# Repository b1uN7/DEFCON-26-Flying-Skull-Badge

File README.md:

DEFCON 26 Flying Skull Badge

__Let's wotk together for DEFCON 29 (2021)!!  I have set up a new Slack fir us to prepare: 
https://join.slack.com/t/flyingbadgers/shared_invite/zt-rhldgde9-1GLsEr0Yzdh6VICE2oVjuQ__

/------------------------------------------------------------------------------------------------\\ 

| . .  . * READ ME * . . . * NO SHIT READ ME * . . . *You will be F#@KED if you don't READ ME!!!*  . . . |

/------------------------------------------------------------------------------------------------\\ 

|--------------------__I have figured the following items out _the hard way_!!!__-----------------------|

/------------------------------------------------------------------------------------------------\\ 

| 1 DO NOT CROSS NEG & POS -/+ there is no protection for this (ie soldering on battery leads!) 

| 2 DO NOT solder RED FCU Board more then 3 SECS!  Diods will POP & NEED TO BUY NEW ONES!

| 3 If RED FCU Board from Syma 5X is solid RED (no blink) when powered see #2!!

| 4 Propellors are different (A & B) be sure to MATCH them to the MOTORS (See badge around motors!)

/------------------------------------------------------------------------------------------------\\

*** QUICK UPDATE: GETTING STARTED WITH YOU BADGE ***                   

*** (AKA GETTING YOUR BADGE STARTED) VIDEO IS NOW POSTED TO WIKI ***

Ok, so if you are here, you are probably looking for flying badge stuff like "how the f*$K do I put this thing together" or "it won't stop bliking, why won't it stop blinking"

This site (in time) will answer all those questions.

For now, until I can get stuff up on Thursday (I won't commit to which Thursday I am talking about) here are the answers to those questions:

Q1: How to put it together?

A1: If you are a hacker, figure it out!  If you are not a hacker, why the f*%K do you have a hacker badge? 

Q2: How do I get this stupid-ass badge to stop blinking?

A2: See Q1

Ok, only kidding.  If you don't have a sense of humor and you expect everything to be perfect, then "this is not the badge you are looking for" <virtual hand swipe>

If you are here, then you probably know me enough to realize if it took me a year longer to get you your badge, then you will have figured out I am behind on the documentation (*WHAT, you say, I DIDN'T DO THE DOCUMENTATION FIRST OR ALONG THE WAY???  WTF???)

So be patient and lets work together.  I will be using this repository's wiki to post a lot of the stuff you are looking for (build instructions, videos, my home address so you can come kick me in the balls for making this stupid badge, etc).  As we are a hacker community, it would be great if we worked together and post all our combined shit there!  PLEASE be and ACTIVE part of this process!!  I encourage you to post, advise, answer, and collectively curse at me for doing this to you!!

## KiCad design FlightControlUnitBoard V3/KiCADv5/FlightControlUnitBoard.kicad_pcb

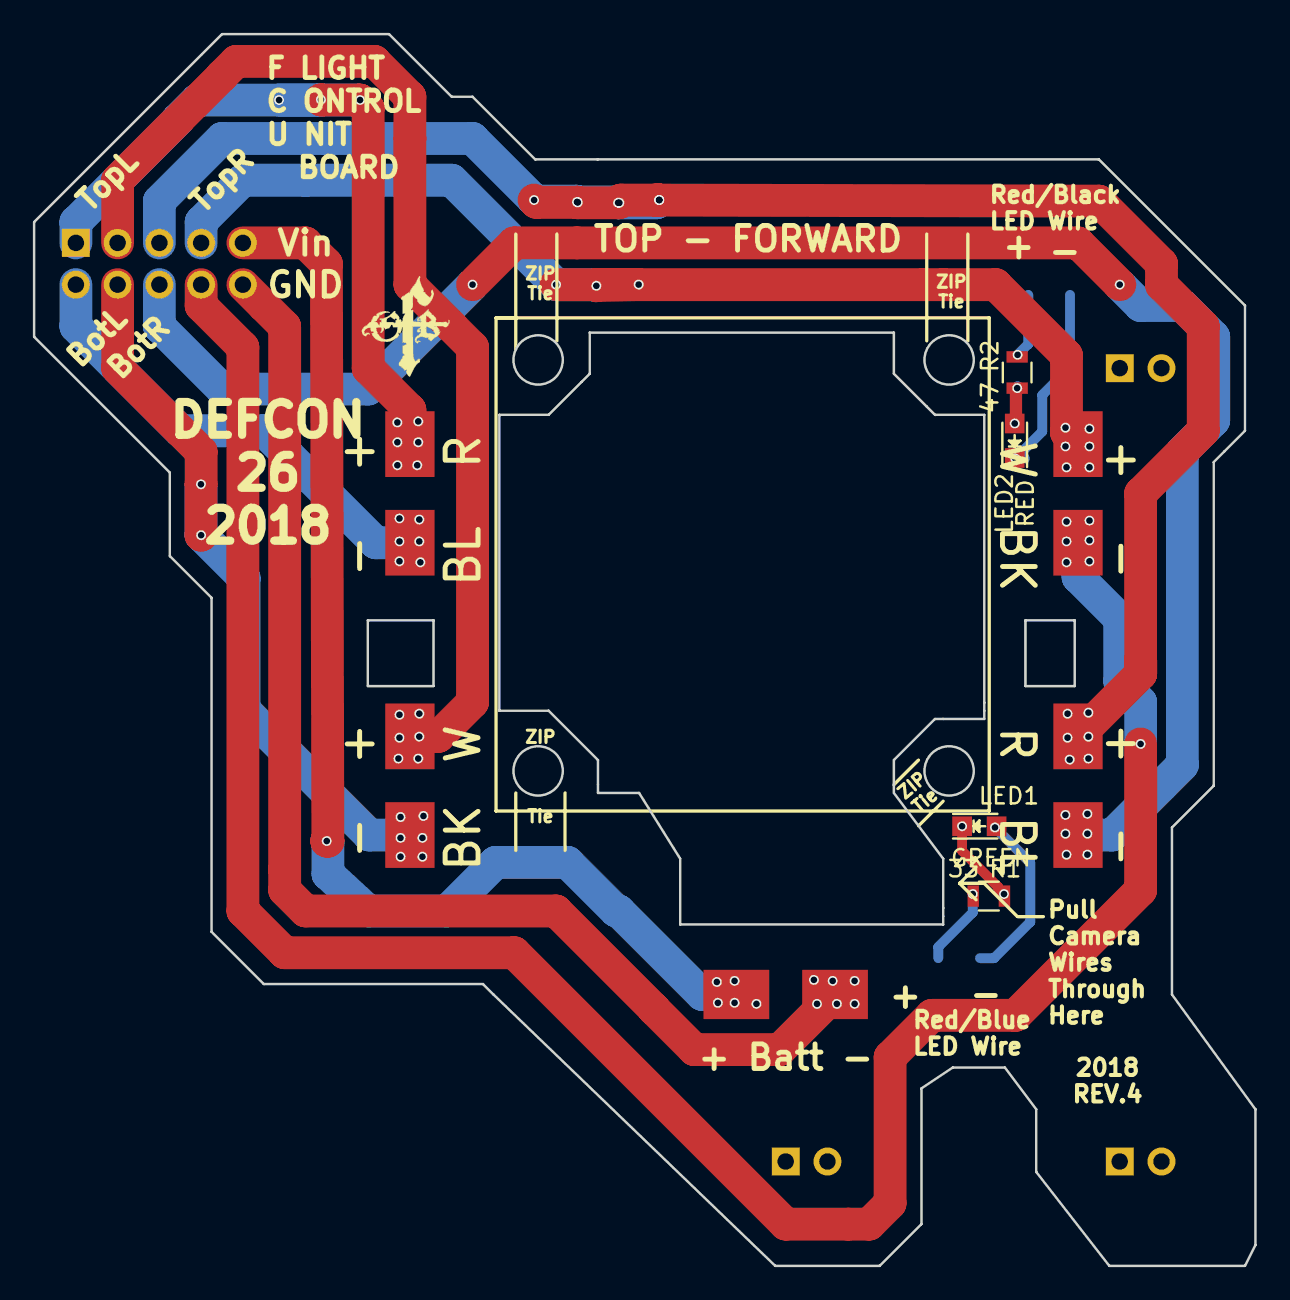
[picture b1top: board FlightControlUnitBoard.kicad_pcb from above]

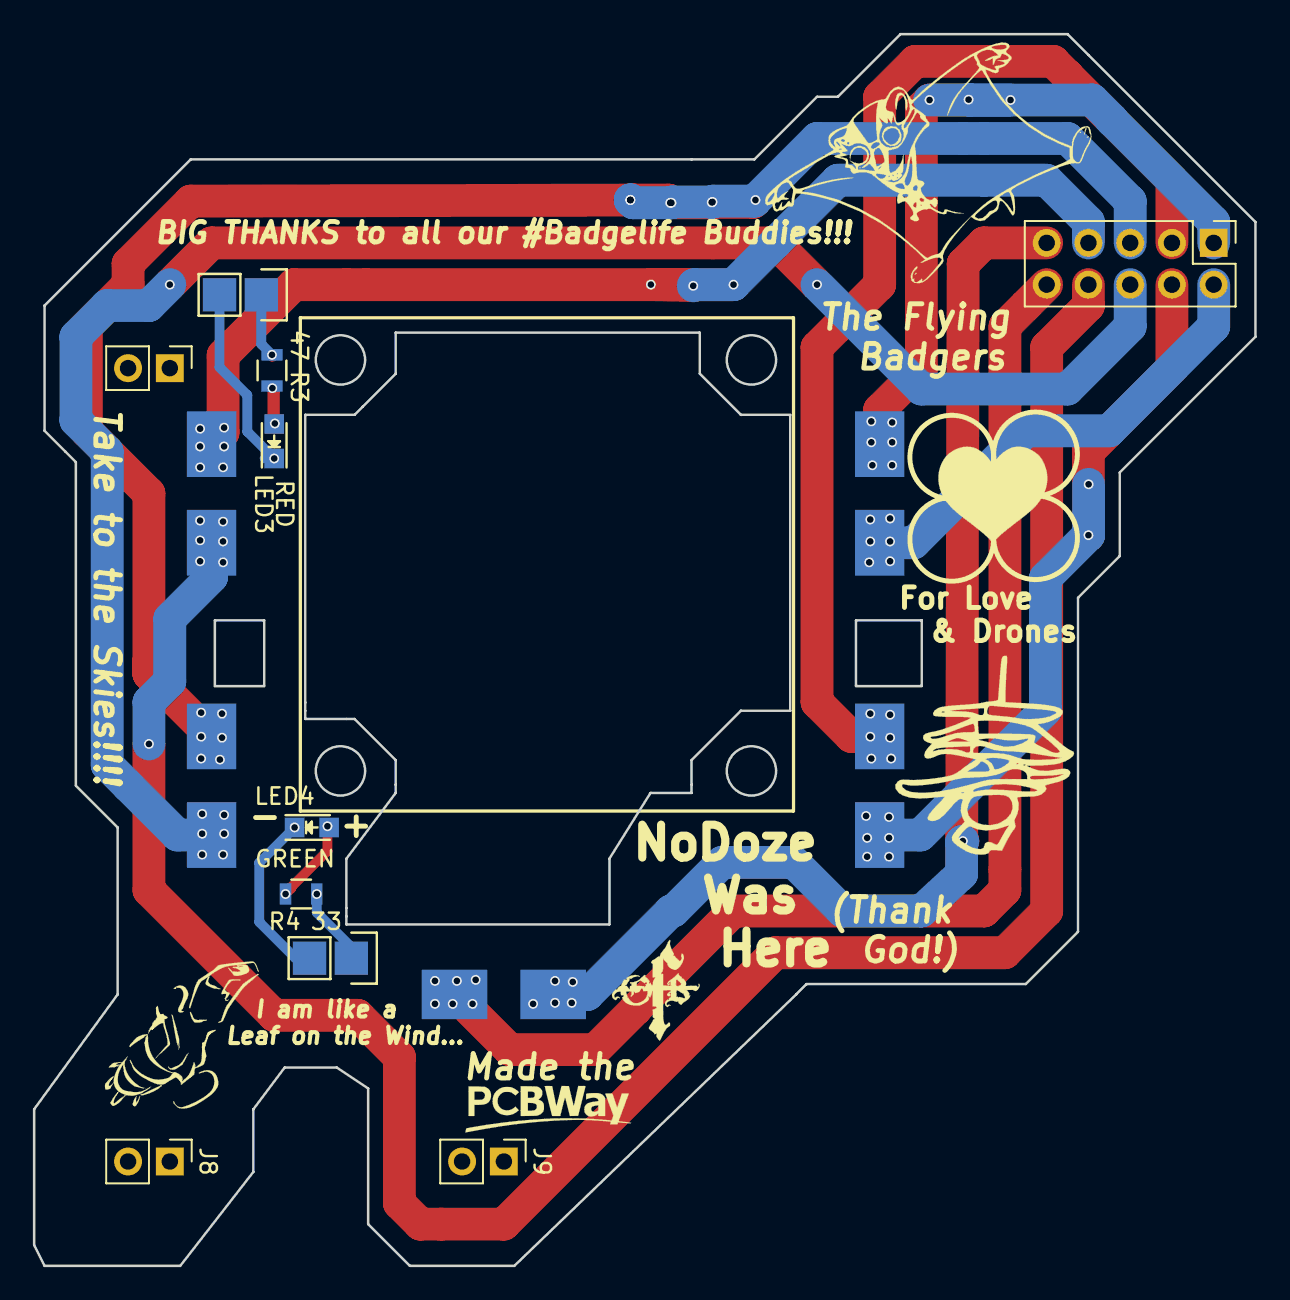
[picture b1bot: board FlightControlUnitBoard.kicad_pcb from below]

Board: 2 copper layers, 74.3 x 74.9 mm, 24 parts (15 on the bottom side), 10 nets.

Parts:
J1: Conn_02x05_Odd_Even; Pin_Header_Straight_2x05_Pitch2.54mm
J2, J2#2, J3, J3#2, J4, J4#2, J5, J5#2, J6, J6#2: Conn_01x02_Male; Wire_Pads_1x2_4x3mm
J7, J8, J9: Conn_02x01; Pin_Header_Straight_1x02_Pitch2.54mm
J10, J11: Pin_Header_Straight_1x02
LED1, LED4: GREEN; LED_0805
LED2, LED3: RED; LED_0805
R1, R4: 33; R_0805
R2, R3: 47; R_0805

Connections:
unnamed: J1.1, J3.1, J3#2.1
unnamed: J1.2, J3.2, J3#2.2
unnamed: J1.3, J4.1, J4#2.1
unnamed: J1.4, J4.2, J4#2.2
unnamed: J1.5, J6.1, J6#2.1
unnamed: J1.6, J6.2, J6#2.2
unnamed: J1.7, J5.1, J5#2.1
unnamed: J1.8, J5.2, J5#2.2
unnamed: J1.9, J2.2, J2#2.2, J9.2
unnamed: J1.10, J2.1, J2#2.1, J9.1

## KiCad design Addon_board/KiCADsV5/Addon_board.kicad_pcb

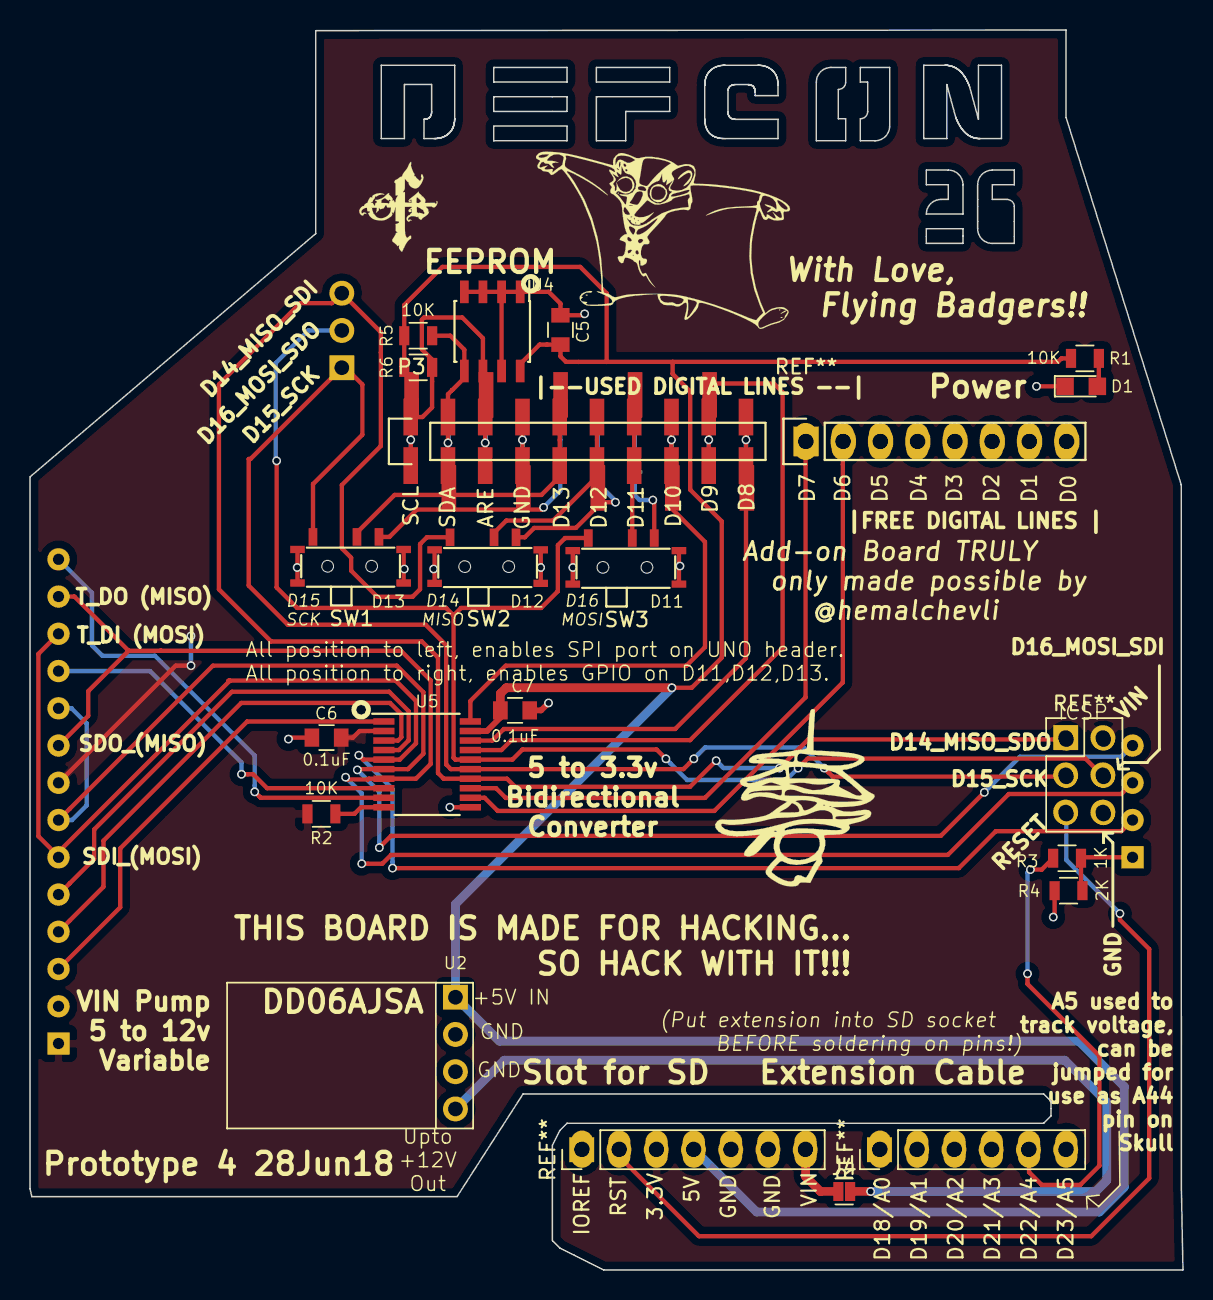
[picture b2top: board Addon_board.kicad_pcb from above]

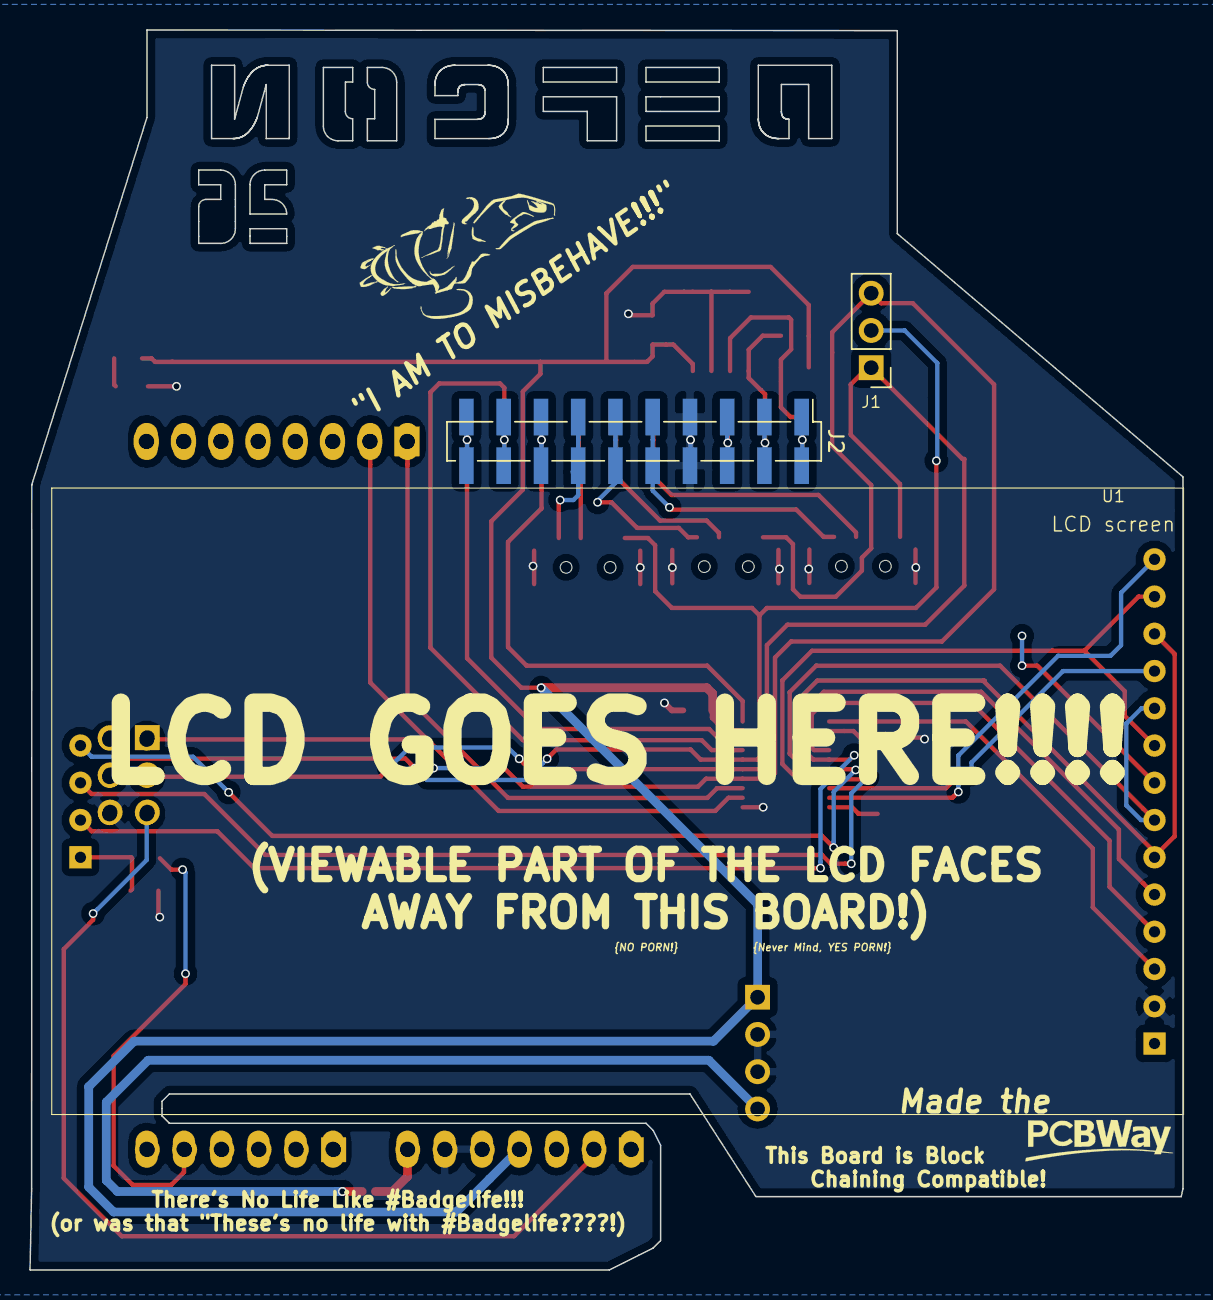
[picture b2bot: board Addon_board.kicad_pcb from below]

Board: 2 copper layers, 78.6 x 84.5 mm, 22 parts (3 on the bottom side), 35 nets.

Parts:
C5: 10 pF; C_0805
C6, C7: 0.1uF; C_0805
D1: LED; LED_0805
J1: SPI; Pin_Header_Straight_1x03_Pitch2.54mm
J2: BottomConn; Pin_Header_Straight_1x10_Pitch2.54mm_SMD_Pin1Left
J4: GS2; SolderJumper
P3: Digital Header 02; Socket_Strip_Straight_1x10_2.54_SMD
R1, R2, R5, R6: 10K; R_0805
R3: 1K; R_0805
R4: 2K; R_0805
SW1, SW2, SW3: SW_SPDT; MSK12C02
U1: 2.4TFT_LCD; 2.4_TFT_LCD_OUTLINE
U2: DD06AJSA; DCDC_BOOST
U4: 24LC256; SOIC-8_3.9x4.9mm_Pitch1.27mm
U5: TXB0108PWR; TSSOP-20_4.4x6.5mm_Pitch0.65mm
XA2: Shield; UNO_headersICSP_EDIT_10smd

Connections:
/+3V3: C6.1, R2.2, U1.1, U1.8, U5.2, XA2.3V3, XA2.SP2
/+5V: C5.1, C7.1, R1.1, R5.2, R6.2, U2.1, U4.8, U5.19, XA2.5V
/+12V: J4.2, U2.4
/A4: R3.1, XA2.A4
/A4_3V3: R3.2, R4.1, U1.15
/AREF: J2.3, XA2.AREF
/D6: U5.12, XA2.D6
/D6_3V3: U1.14, U5.9
/D7: U5.13, XA2.D7
/D7_3V3: U1.11, U5.8
/D8: J2.10, U5.18, XA2.D8
/D8_3V3: U1.4, U5.3
/D9: J2.9, U5.17, XA2.D9
/D9_3V3: U1.5, U5.4
/D10: J2.8, U5.20, XA2.D10
/D10_3V3: U1.3, U5.1
/D11: J2.7, SW3.3
/D12: J2.6, SW2.3
/D13: J2.5, SW1.3
/DD11: SW3.2, XA2.D11
/DD12: SW2.2, XA2.D12
/DD13: SW1.2, XA2.D13
/MISO_3V3: U1.9, U1.13, U1.17, U5.7
/MISO_5V: J1.3, SW2.1, U5.14, XA2.SP1
/MOSI_3V3: U1.6, U1.12, U1.16, U5.5
/MOSI_5V: J1.2, SW3.1, U5.16, XA2.SP4
/SCL: J2.1, R6.1, U4.6, XA2.SCL
/SCLK_3V3: U1.7, U1.10, U1.18, U5.6
/SCLK_5V: J1.1, SW1.1, U5.15, XA2.SP3
/SDA: J2.2, R5.1, U4.5, XA2.SDA
GND: C5.2, C6.2, C7.2, D1.1, J2.4, R4.2, SW1.4, SW2.4, SW3.4, U1.2, U2.2, U2.3, U4.1, U4.2, U4.3, U4.4, U4.7, U5.11, XA2.GND1, XA2.GND2, XA2.GND3, XA2.SP6
unnamed: D1.2, R1.2
unnamed: J4.1, XA2.VIN
unnamed: R2.1, U5.10
unnamed: XA2.RST, XA2.SP5

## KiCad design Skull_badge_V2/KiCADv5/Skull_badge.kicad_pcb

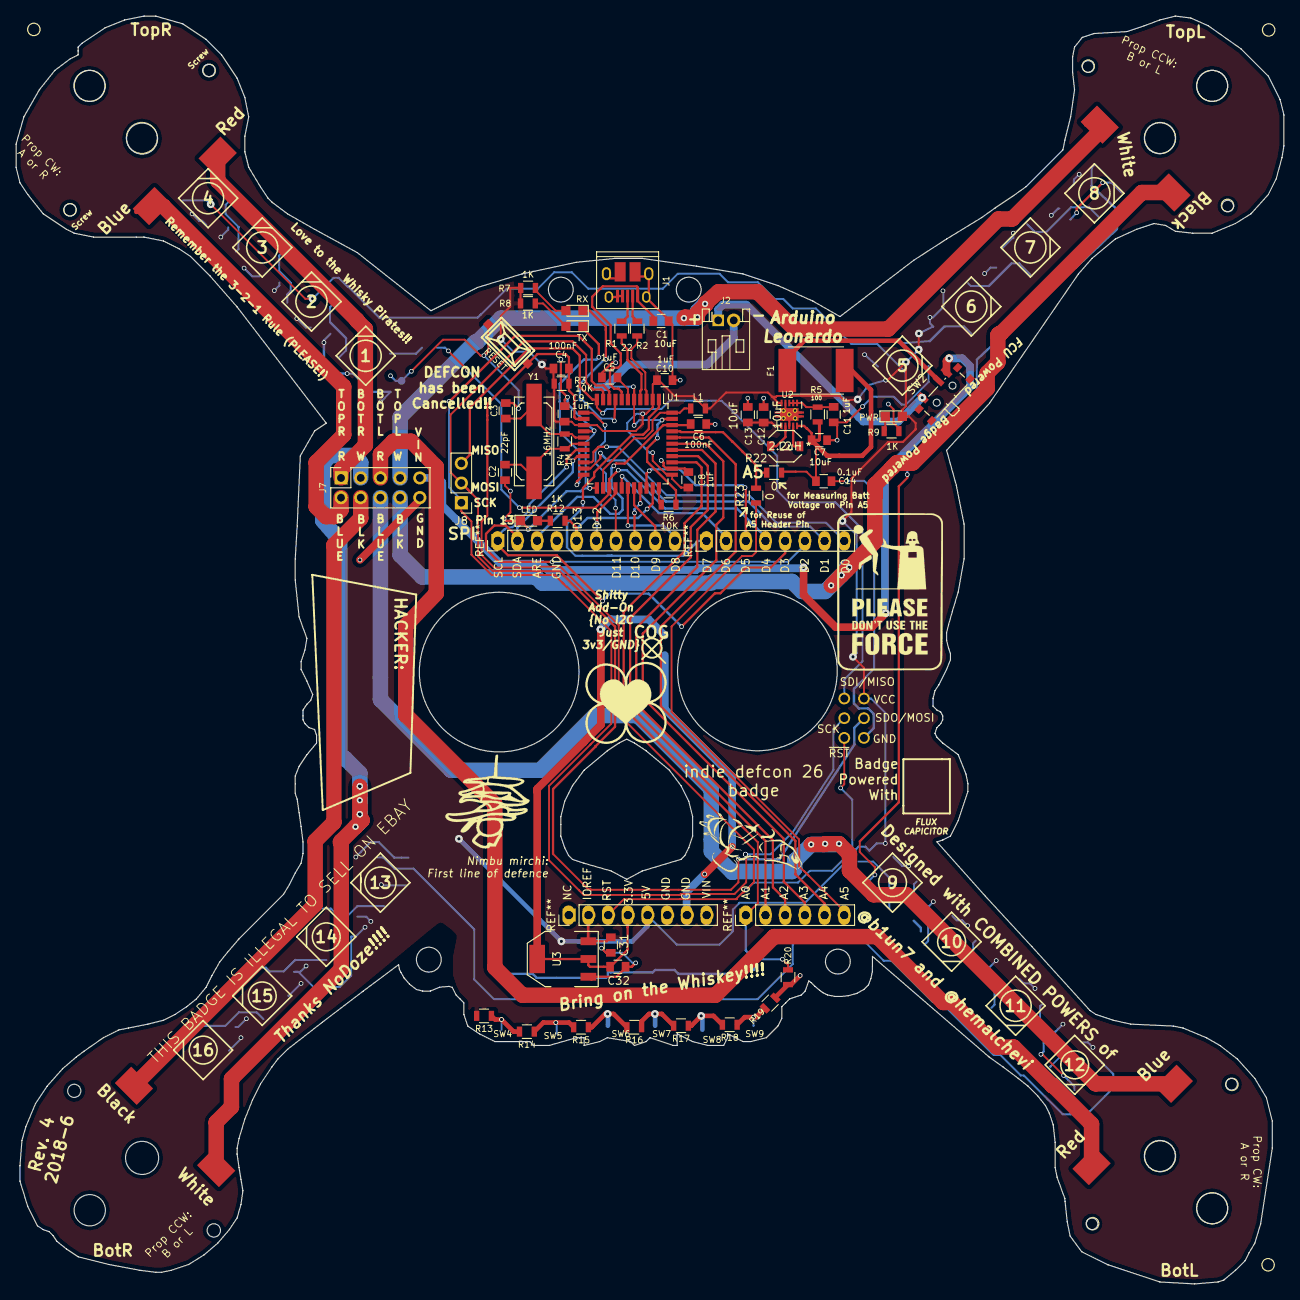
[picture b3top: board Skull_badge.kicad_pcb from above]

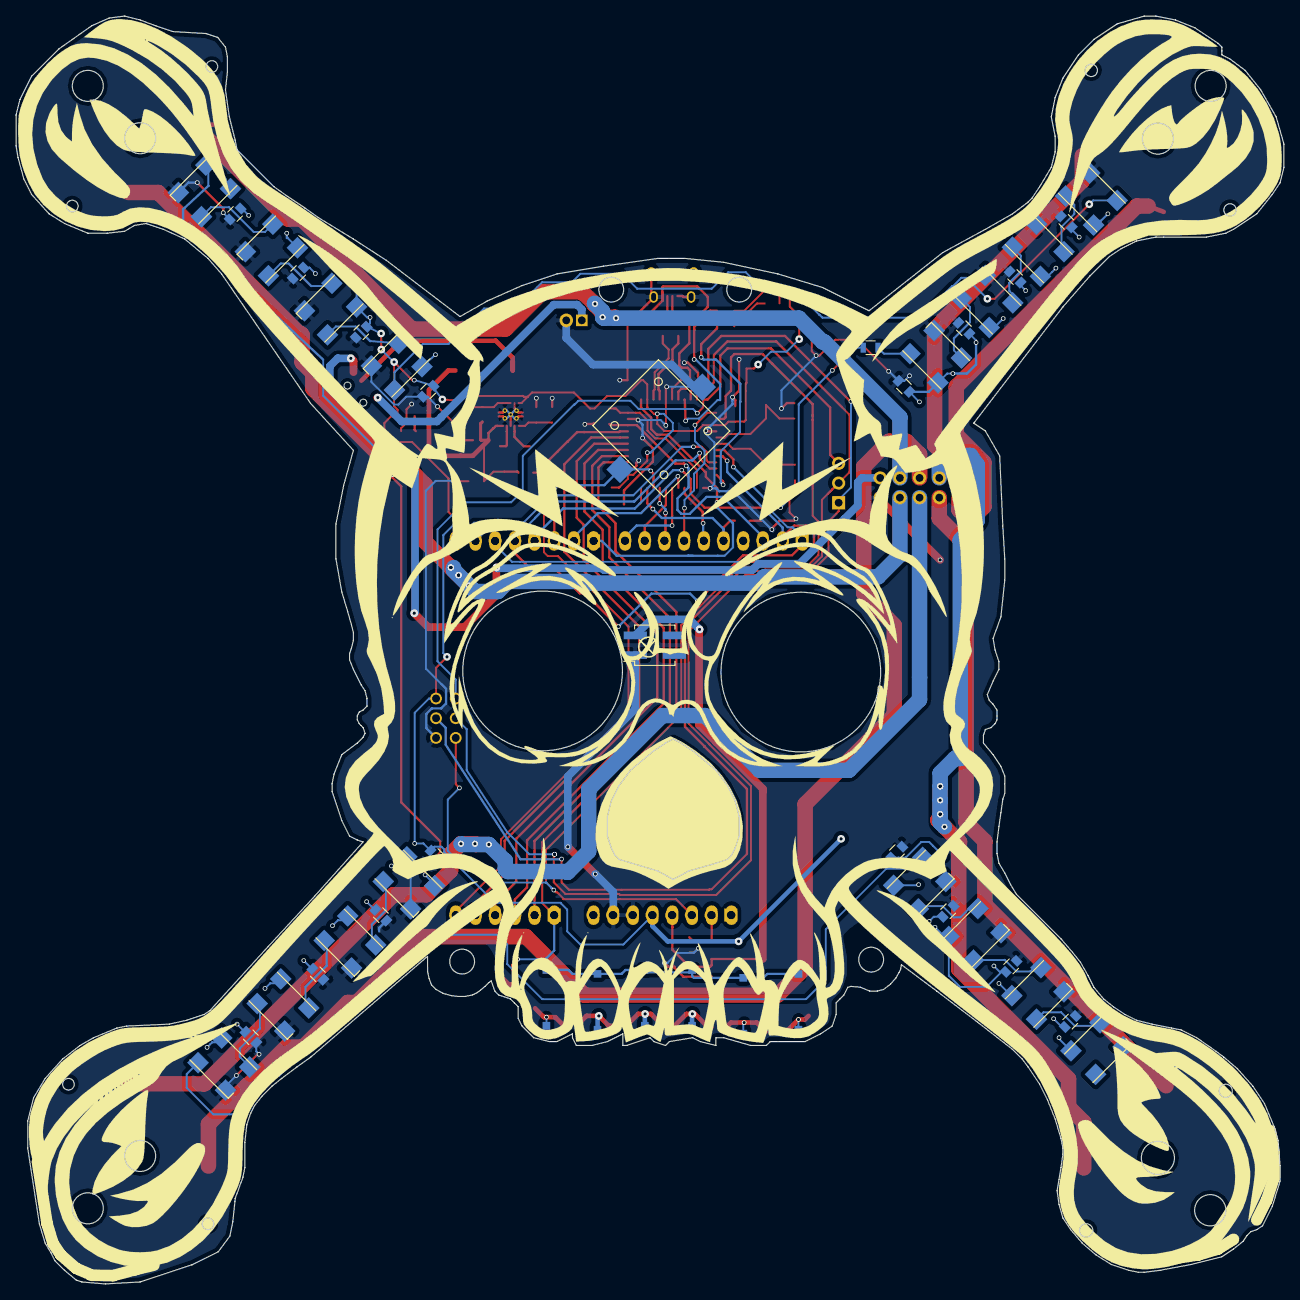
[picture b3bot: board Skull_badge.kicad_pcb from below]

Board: 2 copper layers, 163.5 x 163.5 mm, 101 parts (42 on the bottom side), 79 nets.

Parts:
C1, C7, C12, C13, C31, C32: 10uF; C_0805
C2, C3: 22pF; C_0805
C4, C6: 100nF; C_0805
C5, C8, C9, C10, C11: 1uF; C_0805
C14, C15, C16, C17, C18, C19, C20, C21, C22, C23, C24, C25, C26, C27, C28, C29, C30: 0.1uF; C_0805
D1: RX; LED_0805
D2: TX; LED_0805
D3: PWR; LED_0805
D4: LED; LED_0805
F1: Fuse; Fuse_SMD2920
J1: USB_OTG; USB_Micro-B_10103594-0001LF
J2: LiPo; JST_PH_S2B-PH-K_02x2.00mm_Angled
J3: TopR; Wire_Pads_1x2_4x3mm_Extended
J4: BtmL; Wire_Pads_1x2_4x3mm_Extended
J5: BtmR; Wire_Pads_1x2_4x3mm_Extended
J6: TopL; Wire_Pads_1x2_4x3mm_Extended
J7: Flight Controller Board; Socket_Strip_Straight_2x05_Pitch2.54mm
J8: SPI; Pin_Header_Straight_1x03_Pitch2.54mm
L1: L; L_0805
L2: 2.2uH; VLF4012AT-2R2M1R5
LS1: Speaker_Crystal; piezo_KJL_1325
R1, R2: 22; R_0805
R3, R6: 10K; R_0805
R4, R20: 1M; R_0805
R5: 100; R_0805
R7, R8, R9, R12, R13, R14, R15, R16, R17, R18, R19: 1K; R_0805
R21: 300; R_0805
R22, R23: 0; R_0805
SW1: RESET; smd_push
SW2: ARD_SW; SW_SPDT_PCM12
SW4, SW5, SW6, SW7, SW8, SW9: SW_Push; smd_push
U1: ATMEGA32U4-AU; TQFP-44_10x10mm_Pitch0.8mm
U2: TPS63002; VSON-10-1EP_3x3mm_Pitch0.5mm_ThermalPad
U3: AZ1117-3.3; SOT-223_edit
U5: LOGO; Skull18_150x150
U6: Lime_pepper; lime_pepper
U9, U10, U11, U12, U13, U14, U15, U16, U17, U18, U19, U20, U21, U22, U23, U24: WS2812B; LED_WS2812B-PLCC4_LG_PADS
X1: Badgelife_shitty_connector; Socket_Strip_Straight_2x02_Pitch2.54mm_SMD
XA1: Arduino_Uno_Shield; UNO_headersICSP
Y1: 16MHz; Q_49U3HMS

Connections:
+5V: C4.1, C8.1, C9.1, C10.1, C12.1, C13.1, C15.1, C16.1, C17.1, C18.1, C19.1, C20.1, C21.1, C22.1, C23.1, C24.1, C25.1, C26.1, C27.1, C28.1, C29.1, C30.1, C31.1, D3.2, L1.1, R3.1, R7.2, R8.2, R13.2, U1.2, U1.14, U1.34, U2.1, U2.10, U3.3, U9.1, U10.1, U11.1, U12.1, U13.1, U14.1, U15.1, U16.1, U17.1, U18.1, U19.1, U20.1, U21.1, U22.1, U23.1, U24.1, XA1.5V, XA1.IO, XA1.SP2
/+3V3: C32.1, U3.2, X1.1, XA1.3V3
/+4.2V: J2.1, SW2.1
/+4.2V_ARD: C7.1, C14.1, F1.1, F1.2, R5.2, R22.2, R23.1, SW2.2, U2.5, XA1.A5
/+4.2V_FLT: J7.9, R22.1, R23.2, SW2.3, U1.41
/A1: U1.37, XA1.A1
/A2: U1.38, XA1.A2
/A3: U1.39, XA1.A3
/AREF: C6.1, U1.42, XA1.AREF
/BL1: J4.1, J7.6
/BL2: J4.2, J7.5
/BR1: J5.1, J7.4
/BR2: J5.2, J7.3
/Button_ADC: R20.2, SW4.2, SW5.2, SW6.2, SW7.2, SW8.2, SW9.2, U1.36, XA1.A0
/D0: U1.20, XA1.D0
/D1: U1.21, XA1.D1
/D2_SDA: U1.19, XA1.D2, XA1.SDA
/D3_SCL: U1.18, XA1.D3, XA1.SCL
/D11: U1.12, XA1.D11
/D12: U1.26, XA1.D12
/D13: R12.2, U1.32, XA1.D13
/D+: R1.1, U1.4
/D-: R2.1, U1.3
/LCD_CS: U1.30, XA1.D10
/LCD_DC: U1.29, XA1.D9
/LCD_RESET: U1.28, XA1.D8
/MISO: J8.3, U1.11, XA1.SP1
/MOSI: J8.2, U1.10, XA1.SP4
/Piezo: LS1.1, U1.31, XA1.D5
/RGB_DATA: R21.2, U1.25, XA1.D4
/SCK: J8.1, U1.9, XA1.SP3
/SD_CS: U1.40, XA1.A4
/TL1: J6.1, J7.8
/TL2: J6.2, J7.7
/TOUCH_CS: U1.1, XA1.D7
/TOUCH_IRQ: U1.27, XA1.D6
/TR1: J3.1, J7.2
/TR2: J3.2, J7.1
/VBUS: C1.1, J1.1, U1.7
/xD+: J1.3, R1.2
/xD-: J1.2, R2.2
/~RESET: C4.2, R3.2, SW1.2, U1.13, XA1.RST, XA1.SP5
GND: C1.2, C2.2, C3.2, C5.2, C6.2, C7.2, C8.2, C9.2, C10.2, C11.2, C12.2, C13.2, C14.2, C15.2, C16.2, C17.2, C18.2, C19.2, C20.2, C21.2, C22.2, C23.2, C24.2, C25.2, C26.2, C27.2, C28.2, C29.2, C30.2, C31.2, C32.2, D4.1, J1.4, J1.5, J1.6, J2.2, J7.10, LS1.2, R6.1, R9.1, R19.1, R20.1, SW1.1, U1.5, U1.15, U1.23, U1.35, U1.43, U2.3, U2.9, U2.11, U3.1, U9.3, U10.3, U11.3, U12.3, U13.3, U14.3, U15.3, U16.3, U17.3, U18.3, U19.3, U20.3, U21.3, U22.3, U23.3, U24.3, X1.2, XA1.GND1, XA1.GND2, XA1.SP6
unnamed: C2.1, R4.1, U1.17, Y1.1
unnamed: C3.1, R4.2, U1.16, Y1.2
unnamed: C5.1, U1.6
unnamed: C11.1, R5.1, U2.6, U2.7, U2.8
unnamed: D1.1, U1.8
unnamed: D1.2, R7.1
unnamed: D2.1, U1.22
unnamed: D2.2, R8.1
unnamed: D3.1, R9.2
unnamed: D4.2, R12.1
unnamed: L1.2, U1.24, U1.44
unnamed: L2.1, U2.4
unnamed: L2.2, U2.2
unnamed: R6.2, U1.33
unnamed: R13.1, R14.2, SW4.1
unnamed: R14.1, R15.2, SW5.1
unnamed: R15.1, R16.2, SW6.1
unnamed: R16.1, R17.2, SW7.1
unnamed: R17.1, R18.2, SW8.1
unnamed: R18.1, R19.2, SW9.1
unnamed: R21.1, U11.4
unnamed: U10.2, U14.4
unnamed: U10.4, U24.2
unnamed: U11.2, U15.4
unnamed: U12.2, U16.4
unnamed: U12.4, U23.2
unnamed: U13.2, U17.4
unnamed: U9.2, U13.4
unnamed: U14.2, U18.4
unnamed: U15.2, U19.4
unnamed: U16.2, U20.4
unnamed: U17.2, U21.4
unnamed: U18.2, U22.4
unnamed: U19.2, U23.4
unnamed: U20.2, U24.4
unnamed: U9.4, U22.2

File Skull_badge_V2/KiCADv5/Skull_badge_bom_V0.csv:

Component,Description,Part,References,Value,Footprint,Quantity Per PCB,Datasheet,manf#1,,C_Small,C4 C6 C14 C15 C16 C17 C18 C19 C20 C21 C22 C23 C24 C25 C26 C27 C28 C29 C30,100nF,C_0805,19,,885012207053 885012207060 885012207049 885012207045 885012207056 885012207046 885012207050 885012207057 885012207047 885012207051 885012207054 885012207058 885012207048 885012207052 885012207055 8850122070592,,C_Small,C1 C7 C12 C13,10uF,C_0805,4,,3,,C_Small,C5 C8 C9 C10 C11,1uF,C_0805,5,,4,,C_Small,C2 C3,22pF,C_0805,2,,5,,LED,D4,L,LED_0805,1,,150080YS750006,,LED,D3,PWR,LED_0805,1,,150080YS750007,,LED,D1,RX,LED_0805,1,,150080YS750008,,LED,D2,TX,LED_0805,1,,150080YS750009,,Fuse,F1,Fuse,Fuse_SMD2920,1,,2920L500/16MR10,,Conn_01x02,J4,BtmL,Wire_Pads_1x2_4x3mm_Extended,1,,11,,Conn_01x02,J5,BtmR,Wire_Pads_1x2_4x3mm_Extended,1,,12,,Conn_02x05,J7,Flight Controller Board,Socket_Strip_Straight_2x05_Pitch2.54mm,1,,13,,Conn_01x02,J2,LiPo,JST_PH_S2B-PH-K_02x2.00mm_Angled,1,,14,,Conn_01x03,J8,SPI,Pin_Header_Straight_1x03_Pitch2.54mm,1,,15,,Conn_01x02,J6,TopL,Wire_Pads_1x2_4x3mm_Extended,1,,16,,Conn_01x02,J3,TopR,Wire_Pads_1x2_4x3mm_Extended,1,,17,,USB_OTG,J1,USB_OTG,USB_Micro-B_10103594-0001LF,1,,10103594-0001LF18,,L,L2,2.2uH,VLF4012A,1,,VLF4012AT-2R2M1R519,,L,L1,L,L_0805,1,,BLM21AG601SN1D20,,Speaker_Crystal,LS1,Speaker_Crystal,piezo_KJL_1325,1,,KLJ-132521,,R,R5,100,R_0805,1,,22,,R,R3 R6,10K,R_0805,2,,23,,R,R7 R8 R9 R12 R13 R14 R15 R16 R17 R18 R19,1K,R_0805,11,,24,,R,R4 R10 R20,1M,R_0805,3,,25,,R,R1 R2,22,R_0805,2,,26,,R,R11,2M,R_0805,1,,27,,R,R21,300,R_0805,1,,RC0805JR-07300RL28,,SW_SPDT,SW2,ARD_SW,switch_MHSS1105,1,,MHSS110529,,SW_SPDT,SW3,FLT CTRL SW,switch_MHSS1105,1,,MHSS110530,,SW_Push,SW1,RESET,smd_push,1,,MJTP1106STR31,,SW_Push,SW4 SW5 SW6 SW7 SW8 SW9,SW_Push,smd_push,6,,MJTP1106STR32,"TQFP44, 16K Flash, 1.25K SRAM, 512B EEPROM, USB2.0",ATMEGA32U4-AU,U1,ATMEGA32U4-AU,TQFP-44_10x10mm_Pitch0.8mm,1,http://www.atmel.com/images/atmel-7766-8-bit-avr-atmega16u4-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,ATMEGA32U4-AUR33,,TPS63001,U2,TPS63001,VSON-10-1EP_3x3mm_Pitch0.5mm_ThermalPad,1,,TPS63002DRCT34,,WS2812B,U9 U10 U11 U12 U13 U14 U15 U16 U17 U18 U19 U20 U21 U22 U23 U24,WS2812B,LED_WS2812B-PLCC4,16,,165535,,Conn_02x02,X1,Badgelife_shitty_connector,Socket_Strip_Straight_2x02_Pitch2.54mm,1,,36,,Arduino_Uno_Shield,XA1,Arduino_Uno_Shield,"UNO_headersICSP: (2) Socket_Strip 1x08, (1) Socket_Strip 1x06, (1) Socket_Strip 1x10, (1) Header_Pins 02x03",1,,37,,Crystal,Y1,16MHz,Q_49U3HMS,1,,ABLS-16.000MHZ-B4-T,,,,,,,,,,,,,,,,,,,,,,,,,,,,,,,,,,,,,,,,Component Groups:,39,,,,,,,Component Count:,99,,,,,,,Fitted Components:,99,,,,,,,Number of PCBs:,1,,,,,,,Total components:,99,,,,,,,Schematic Version:,V0,,,,,,,Schematic Date:,5/14/18,,,,,,,BoM Date:,"Monday, June 11, 2018 'PMt' 04:22:07 PM",,,,,,,Schematic Source:,/Users/rscote/Dropbox/DC26/FlyingSkull/gitlab/Skull_badge_V2/Skull_badge.sch,,,,,,,KiCad Version:,Eeschema 4.0.7,,,,,,,

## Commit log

2018-08-18 initial upload
    cleaned up up folders

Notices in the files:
parts and their libraries:
Copyright 2016 Accelerated Designs. All rights reserved.
